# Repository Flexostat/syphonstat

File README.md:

usage
=====

main.py:

Note that currently this is rough code and as such you have to modify some code constats to change settings.

All configureation is in main.py toward the top.  These variables are clearly labeled.  Currently the only adjustable things are the serial port used and the OD setpoint.

To run, make sure the correct serial port is setup and execute main.py (eg in a terminal, type 'python main.py' without the single quotes).

plot.py:

Used to quickely plot data generated by main.py.  Assuming numpy/scipy are installed, just run 'python plot.py'.

<br />This work is licensed under a <a rel="license" href="http://creativecommons.org/licenses/by/4.0/">Creative Commons Attribution 4.0 International License</a>.

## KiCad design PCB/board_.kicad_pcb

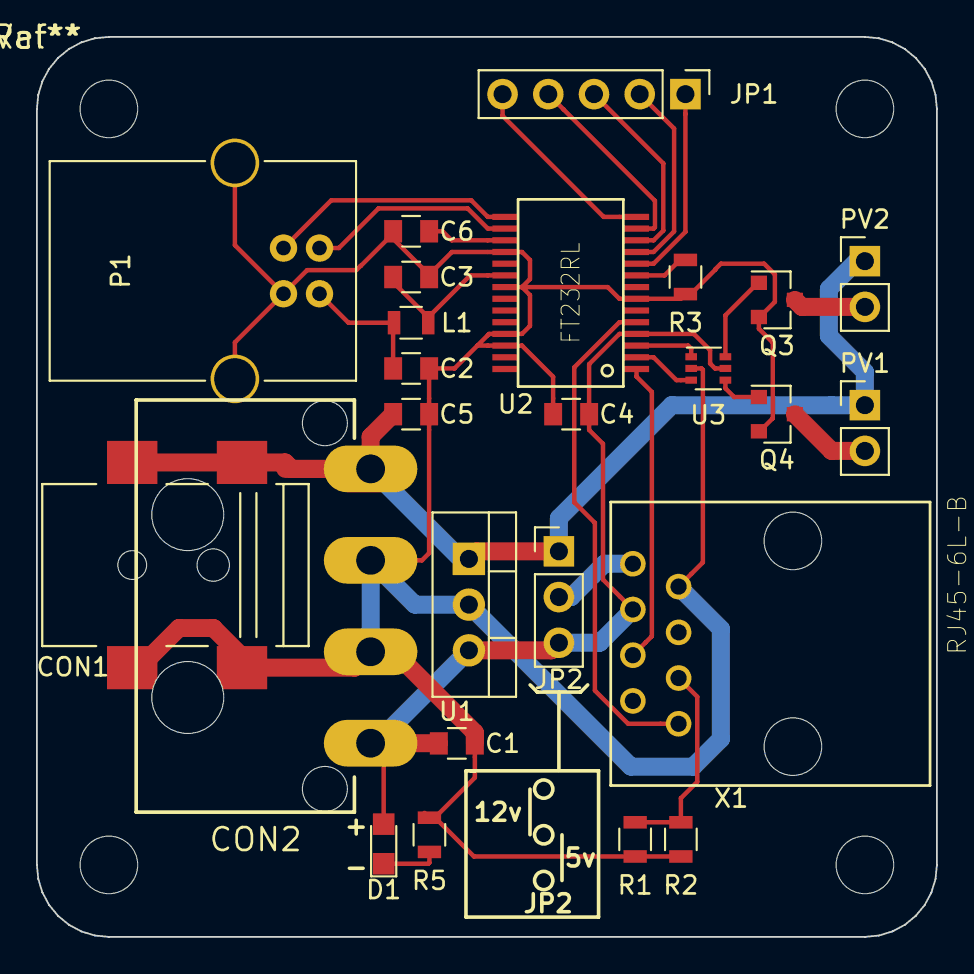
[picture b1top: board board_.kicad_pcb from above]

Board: 2 copper layers, 50.0 x 50.0 mm, 26 parts (0 on the bottom side), 25 nets.

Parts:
C1, C3, C6: .1uF; C_0805
C2: 0.01uF; C_0805
C4, C5: 4.7uF; C_0805
CON1: BARREL_JACK; CUI_PJ-002BH-SMT-TR
CON2: 9090-4R; con-thomas-betts-9090-4R
D1: LED; LED_0805
JP1: Pin_Header_Straight_1x05_Pitch2.54mm
JP2: Pin_Header_Straight_1x03_Pitch2.54mm
L1: MI0805K400R-10; R_0805
P1: USB_B
PV1, PV2: Pin_Header_Straight_1x02_Pitch2.54mm
Q3, Q4: Q_NMOS_GSD; SOT-23
R1: 390; R_0805
R2: 330; R_0805
R3, R5: R_0805
Ref**: Val**; DP5050
U1: R-78x05; TO-220_Vertical
U2: FT232RL; SSOP28-LD
U3: 74HCT2G04; SOT-363_SC-70-6
X1: RJ45-6L-B; 54602-908LF

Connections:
+5V: C1.1, C4.1, CON2.1, D1.2, JP2.3, U1.3, U2.4, U3.5, X1.6
+12V: C5.1, CON1.1, CON2.4, JP2.1, PV1.1, PV2.1, U1.1
/RX1E: U2.5, X1.1
/TX1: U2.1, X1.4
GND: C1.2, C2.2, C3.2, C4.2, C5.2, C6.2, CON1.2, CON1.3, CON2.2, CON2.3, P1.4, P1.5, Q3.2, Q4.2, R1.2, R2.2, R3.2, R5.2, U1.2, U2.7, U2.18, U2.21, U2.25, U2.26, U3.2, X1.7
unnamed: JP2.2, X1.8
unnamed: C2.1, L1.1, P1.1
unnamed: C3.1, L1.2, U2.20
unnamed: C6.1, U2.17
unnamed: D1.1, R5.1
unnamed: JP1.1, U2.10
unnamed: JP1.2, U2.11
unnamed: JP1.3, U2.12
unnamed: JP1.4, U2.13
unnamed: JP1.5, U2.14
unnamed: P1.2, U2.16
unnamed: P1.3, U2.15
unnamed: PV1.2, Q4.3
unnamed: PV2.2, Q3.3
unnamed: Q3.1, U3.6
unnamed: Q4.1, U3.4
unnamed: R1.1, R2.1, X1.3
unnamed: R3.1, U2.9
unnamed: U2.2, U3.3
unnamed: U2.3, U3.1

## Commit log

2014-02-21 first test file
2014-02-21 test commit
2014-02-21 commited firmware
2014-02-21 stub main python
2014-02-21 first version of syphon chemostat
2014-02-22 added turbidostat mode. added simple plotter
2014-02-24 some bugfixes
2014-02-24 corrected exception handler
2014-02-24 now saves state between runs
2014-02-25 fixed typo bug and made u saturate so it doesn't cause an integer overflow
2014-02-25 fixed whitespace issue. made saving state more robust to poorly timed keyboard interrupt
2014-12-19 Removed firmware since it is now integrated
2014-12-19 added note
2014-12-19 wrote minimal documentation.
2015-01-05 added PV1 support
2015-01-06 made controller PV port use optional
2015-02-13 added commandline flags
2015-02-13 test mode bug fix
2015-02-13 updated git ignore
2015-02-13 added usage docs
2015-02-18 added secret option -g
2015-02-18 fixed bug in -g
2015-02-20 new -g logic
2015-02-20 new gains
2015-09-10 updated code for v1.1 support
2015-09-14 added optional top for holding PV
2016-10-02 updated enclosure
2017-03-25 fixed git ignore to ignore temp files from vim
2017-03-25 changed default com port
2017-03-25 added .csv
2017-03-25 added csv_convert, converts json-like logs to csv
2017-07-25 version detection more clear
2018-10-22 added exclusings for kicad
2018-10-22 PCB files
2018-10-23 added bom
2020-03-09 added CC-BY
